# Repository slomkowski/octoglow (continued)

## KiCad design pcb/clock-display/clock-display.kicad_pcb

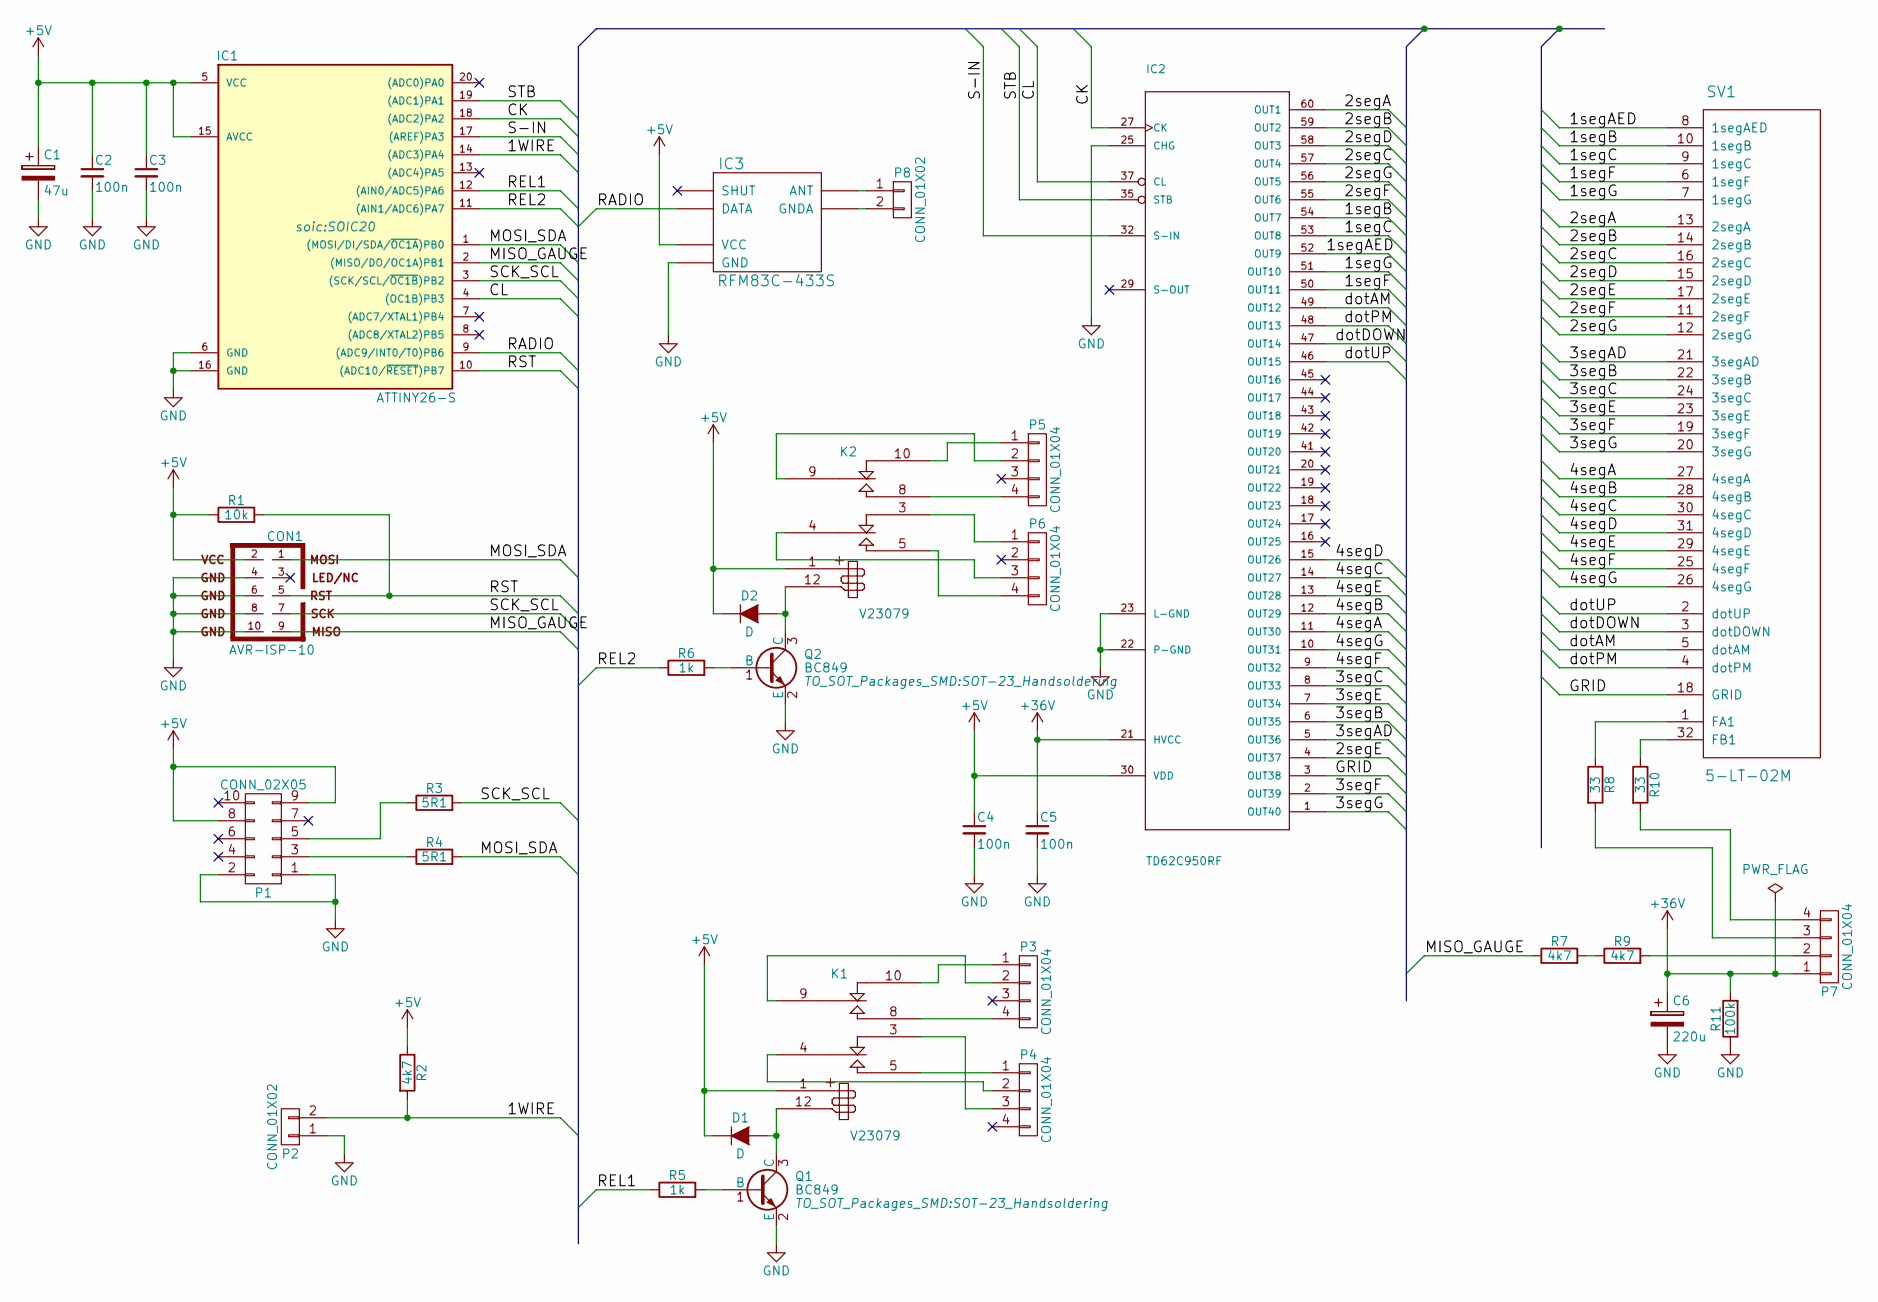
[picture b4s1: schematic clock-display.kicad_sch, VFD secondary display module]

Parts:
C1: 47u; c_elec_8x10
C2, C3, C4, C5: 100n; C_1206_HandSoldering
C6: 220u; c_elec_10x10
CON1: AVR-ISP-10; Pin_Header_Straight_2x05_Pitch2.54mm
D1, D2: D; SMA_Handsoldering
IC1: ATTINY26-S; SOIC20
IC2: TD62C950RF; TD62C950RF-SSOP60-P-0.65A
IC3: RFM83C-433S; RFM83C_standard
K1, K2: V23079; V23098-SMT-long
P1: CONN_02X05; Pin_Header_Straight_2x05_Pitch2.54mm
P2, P8: CONN_01X02; Pin_Header_Straight_1x02_Pitch2.54mm
P3, P4, P7: CONN_01X04; 0-188275-4_SMD_4-pin_female
P5, P6: CONN_01X04; 0-215464-4_TH_4-pin_male
Q1, Q2: BC849; SOT-23_Handsoldering
R1: 10k; R_1206_HandSoldering
R2, R7, R9: 4k7; R_1206_HandSoldering
R3, R4: 5R1; R_1206_HandSoldering
R5, R6: 1k; R_1206_HandSoldering
R8, R10: 33; Resistor_Horizontal_RM15mm
R11: 100k; R_1206_HandSoldering
SV1: 5-LT-02M; futaba-vfd-5-LT-02

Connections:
+5V: C1.1, C2.1, C3.1, C4.1, CON1.2, D1.1 (K), D2.1 (K), IC1.5 (VCC), IC1.15 (AVCC), IC2.30 (VDD), IC2.31 (VDD), IC3.4 (VCC), K1.1 (+), K2.1 (+), P1.8, P1.9, R1.1, R2.1
+36V: C5.1, C6.1, IC2.21 (HVCC), IC2.40 (HVCC), P7.1, R11.2
/1WIRE: IC1.14 ((ADC3)PA4), P2.2, R2.2
/1segAED: IC2.52 (OUT9), SV1.8 (1segAED)
/1segB: IC2.54 (OUT7), SV1.10 (1segB)
/1segC: IC2.53 (OUT8), SV1.9 (1segC)
/1segF: IC2.50 (OUT11), SV1.6 (1segF)
/1segG: IC2.51 (OUT10), SV1.7 (1segG)
/2segA: IC2.60 (OUT1), SV1.13 (2segA)
/2segB: IC2.59 (OUT2), SV1.14 (2segB)
/2segC: IC2.57 (OUT4), SV1.16 (2segC)
/2segD: IC2.58 (OUT3), SV1.15 (2segD)
/2segE: IC2.4 (OUT37), SV1.17 (2segE)
/2segF: IC2.55 (OUT6), SV1.11 (2segF)
/2segG: IC2.56 (OUT5), SV1.12 (2segG)
/3segAD: IC2.5 (OUT36), SV1.21 (3segAD)
/3segB: IC2.6 (OUT35), SV1.22 (3segB)
/3segC: IC2.8 (OUT33), SV1.24 (3segC)
/3segE: IC2.7 (OUT34), SV1.23 (3segE)
/3segF: IC2.2 (OUT39), SV1.19 (3segF)
/3segG: IC2.1 (OUT40), SV1.20 (3segG)
/4segA: IC2.11 (OUT30), SV1.27 (4segA)
/4segB: IC2.12 (OUT29), SV1.28 (4segB)
/4segC: IC2.14 (OUT27), SV1.30 (4segC)
/4segD: IC2.15 (OUT26), SV1.31 (4segD)
/4segE: IC2.13 (OUT28), SV1.29 (4segE)
/4segF: IC2.9 (OUT32), SV1.25 (4segF)
/4segG: IC2.10 (OUT31), SV1.26 (4segG)
/CK: IC1.18 ((ADC2)PA2), IC2.27 (CK)
/CL: IC1.4 ((OC1B)PB3), IC2.37 (CL)
/GRID: IC2.3 (OUT38), SV1.18 (GRID)
/MISO_GAUGE: CON1.9, IC1.2 ((MISO/DO/OC1A)PB1), R7.1
/MOSI_SDA: CON1.1, IC1.1 ((MOSI/DI/SDA/~OC1A)PB0), R4.2
/RADIO: IC1.9 ((ADC9/INT0/T0)PB6), IC3.5 (DATA)
/REL1: IC1.12 ((AIN0/ADC5)PA6), R5.1
/REL2: IC1.11 ((AIN1/ADC6)PA7), R6.1
/RST: CON1.5, IC1.10 ((ADC10/~RESET)PB7), R1.2
/S-IN: IC1.17 ((AREF)PA3), IC2.32 (S-IN)
/SCK_SCL: CON1.7, IC1.3 ((SCK/SCL/~OC1B)PB2), R3.2
/STB: IC1.19 ((ADC1)PA1), IC2.35 (STB)
/dotAM: IC2.49 (OUT12), SV1.5 (dotAM)
/dotDOWN: IC2.47 (OUT14), SV1.3 (dotDOWN)
/dotPM: IC2.48 (OUT13), SV1.4 (dotPM)
/dotUP: IC2.46 (OUT15), SV1.2 (dotUP)
GND: C1.2, C2.2, C3.2, C4.2, C5.2, C6.2, CON1.4, CON1.6, CON1.8, CON1.10, IC1.6 (GND), IC1.16 (GND), IC2.22 (P-GND), IC2.23 (L-GND), IC2.25 (CHG), IC2.38 (L-GND), IC2.39 (P-GND), IC3.6 (GND), P1.1, P1.2, P2.1, Q1.2 (E), Q2.2 (E), R11.1
unnamed: D1.2 (A), K1.12 (-), Q1.3 (C)
unnamed: D2.2 (A), K2.12 (-), Q2.3 (C)
unnamed: IC3.1 (ANT), P8.1
unnamed: IC3.2 (GNDA), P8.2
unnamed: K1.4 (C1), P4.2
unnamed: K1.9 (C2), P3.2
unnamed: K1.3 (R1), P4.3
unnamed: K1.10 (R2), P3.1
unnamed: K1.5 (T1), P4.1
unnamed: K1.8 (T2), P3.4
unnamed: K2.4 (C1), P6.3
unnamed: K2.9 (C2), P5.2
unnamed: K2.3 (R1), P6.1
unnamed: K2.10 (R2), P5.1
unnamed: K2.5 (T1), P6.4
unnamed: K2.8 (T2), P5.4
unnamed: P1.3, R4.1
unnamed: P1.5, R3.1
unnamed: P7.2, R9.2
unnamed: P7.3, R8.2
unnamed: P7.4, R10.2
unnamed: Q1.1 (B), R5.2
unnamed: Q2.1 (B), R6.2
unnamed: R7.2, R9.1
unnamed: R8.1, SV1.1 (FA1)
unnamed: R10.1, SV1.32 (FB1)

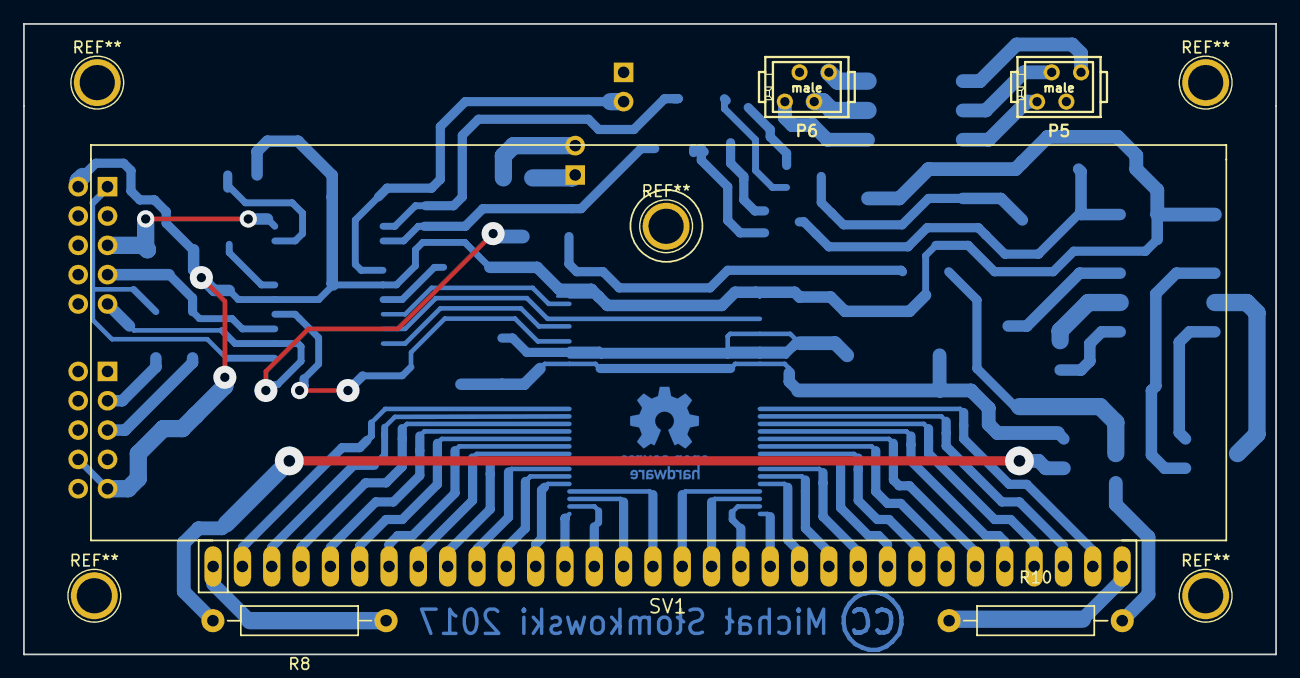
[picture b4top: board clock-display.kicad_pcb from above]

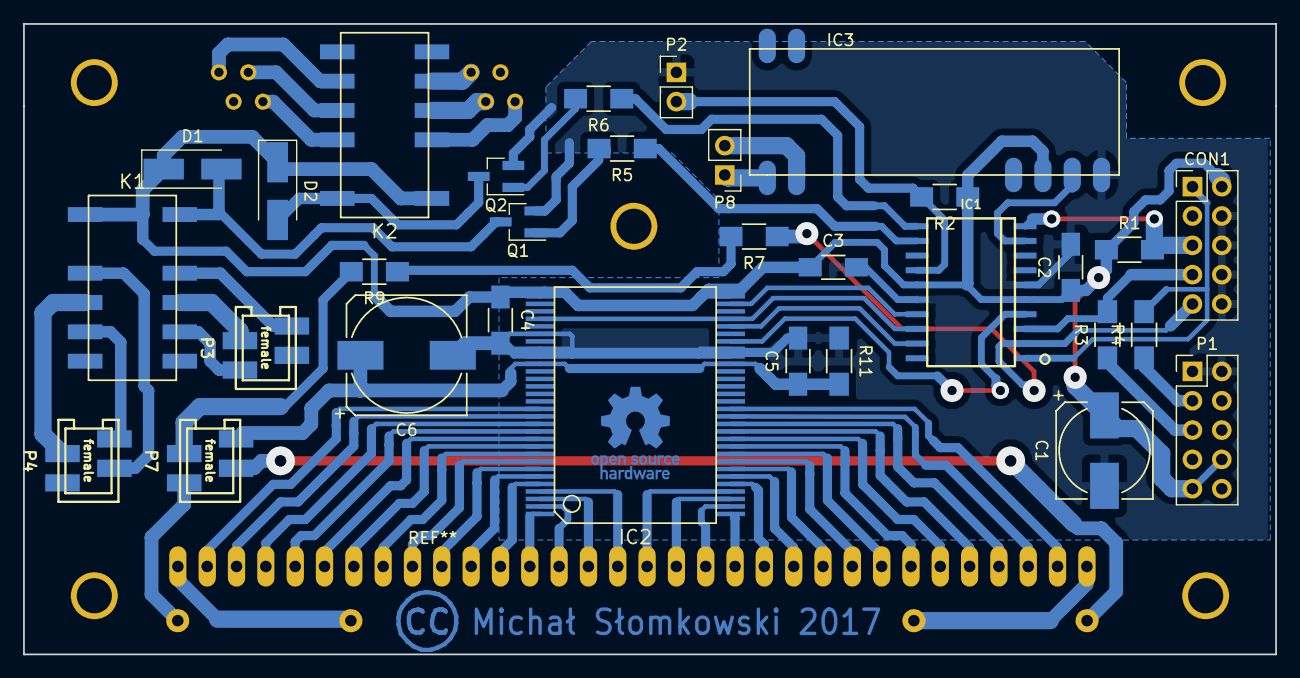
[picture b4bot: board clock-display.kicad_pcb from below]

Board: 2 copper layers, 108.5 x 54.6 mm, 36 parts (31 on the bottom side), 71 nets.

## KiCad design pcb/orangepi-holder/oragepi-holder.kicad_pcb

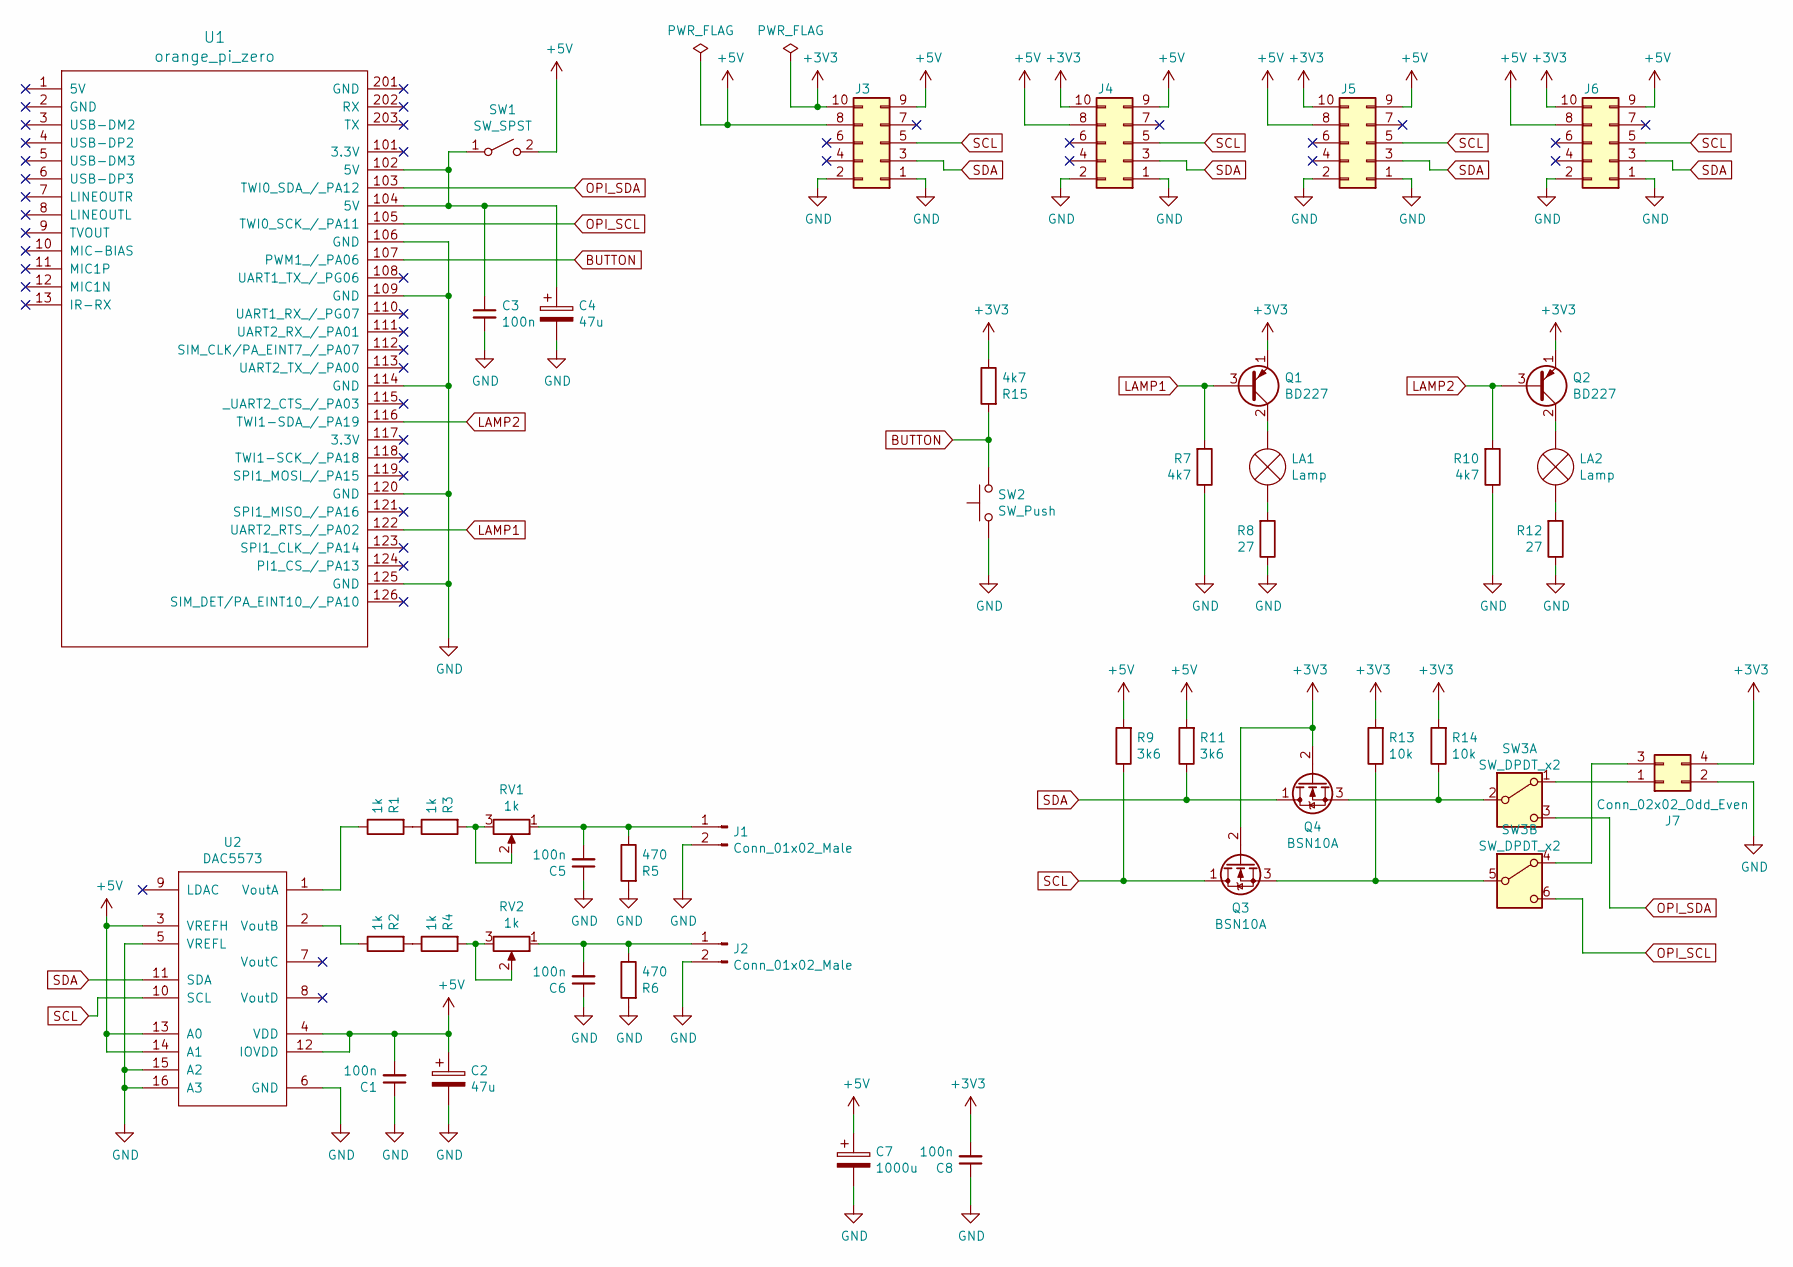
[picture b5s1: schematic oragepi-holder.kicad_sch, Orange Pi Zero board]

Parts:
C1, C3, C5, C6, C8: 100n; C_1206_HandSoldering
C2, C4: 47u; CP_Radial_D7.5mm_P2.50mm
C7: 1000u; CP_Axial_L30.0mm_D10.0mm_P35.00mm_Horizontal
J1, J2: Conn_01x02_Male; Pin_Header_Angled_1x02_Pitch2.54mm
J3, J4, J5, J6: Conn_02x05_Odd_Even; IDC-Header_2x05_P2.54mm_Vertical
J7: Conn_02x02_Odd_Even; 0-215464-4_TH_4-pin_male
LA1, LA2: Lamp; Pin_Header_Straight_1x02_Pitch2.00mm
Q1, Q2: BD227; TO-126_Vertical
Q3, Q4: BSN10A; TO-92_Molded_Wide_Oval
R1, R2, R3, R4: 1k; R_1206_HandSoldering
R5, R6: 470; R_1206_HandSoldering
R7, R10: 4k7; R_1206_HandSoldering
R8, R12: 27; R_Axial_DIN0414_L11.9mm_D4.5mm_P15.24mm_Horizontal
R9, R11: 3k6; R_Axial_DIN0411_L9.9mm_D3.6mm_P15.24mm_Horizontal
R13, R14: 10k; R_Axial_DIN0411_L9.9mm_D3.6mm_P15.24mm_Horizontal
R15: 4k7; R_Axial_DIN0411_L9.9mm_D3.6mm_P15.24mm_Horizontal
RV1, RV2: 1k; SP5-2
SW1: SW_SPST; SPDT
SW2: SW_Push; SPDT
SW3: SW_DPDT_x2; APEM_5246
U1: orange_pi_zero; orangepi-zero
U2: DAC5573; TSSOP-16_4.4x5mm_Pitch0.65mm

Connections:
+3V3: C8.2, J3.10, J4.10, J5.10, J6.10, J7.4, Q1.1 (E), Q2.1 (E), Q3.2 (G), Q4.2 (G), R13.2, R14.2, R15.1
+5V: C1.2, C2.1, C7.1, J3.8, J3.9, J4.8, J4.9, J5.8, J5.9, J6.8, J6.9, R9.2, R11.2, SW1.2 (B), U2.3 (VREFH), U2.4 (VDD), U2.12 (IOVDD), U2.13 (A0), U2.14 (A1)
BUTTON: R15.2, SW2.2, U1.107 (PWM1_/_PA06)
GND: C1.1, C2.2, C3.2, C4.2, C5.1, C6.1, C7.2, C8.1, J1.2, J2.2, J3.1, J3.2, J4.1, J4.2, J5.1, J5.2, J6.1, J6.2, J7.2, R5.2, R6.2, R7.1, R8.1, R10.1, R12.1, SW2.1, U1.106 (GND), U1.109 (GND), U1.114 (GND), U1.120 (GND), U1.125 (GND), U2.5 (VREFL), U2.6 (GND), U2.15 (A2), U2.16 (A3)
LAMP1: Q1.3 (B), R7.2, U1.122 (UART2_RTS_/_PA02)
LAMP2: Q2.3 (B), R10.2, U1.116 (TWI1-SDA_/_PA19)
unnamed: C5.2, J1.1, R5.1, RV1.1
unnamed: C6.2, J2.1, R6.1, RV2.1
unnamed: J7.1, SW3.1 (A)
unnamed: J7.3, SW3.4 (A)
unnamed: LA1.2 (+), Q1.2 (C)
unnamed: LA1.1 (-), R8.2
unnamed: LA2.2 (+), Q2.2 (C)
unnamed: LA2.1 (-), R12.2
unnamed: Q3.3 (S), R13.1, SW3.5 (B)
unnamed: Q4.3 (S), R14.1, SW3.2 (B)
unnamed: R1.2, R3.1
unnamed: R2.2, R4.1
unnamed: R3.2, RV1.2, RV1.3
unnamed: R4.2, RV2.2, RV2.3
unnamed: C3.1, C4.1, SW1.1 (A), U1.102 (5V), U1.104 (5V)
unnamed: R1.1, U2.1 (VoutA)
unnamed: R2.1, U2.2 (VoutB)
OPI_SCL: SW3.6 (C), U1.105 (TWI0_SCK_/_PA11)
OPI_SDA: SW3.3 (C), U1.103 (TWI0_SDA_/_PA12)
SCL: J3.5, J4.5, J5.5, J6.5, Q3.1 (D), R9.1, U2.10 (SCL)
SDA: J3.3, J4.3, J5.3, J6.3, Q4.1 (D), R11.1, U2.11 (SDA)

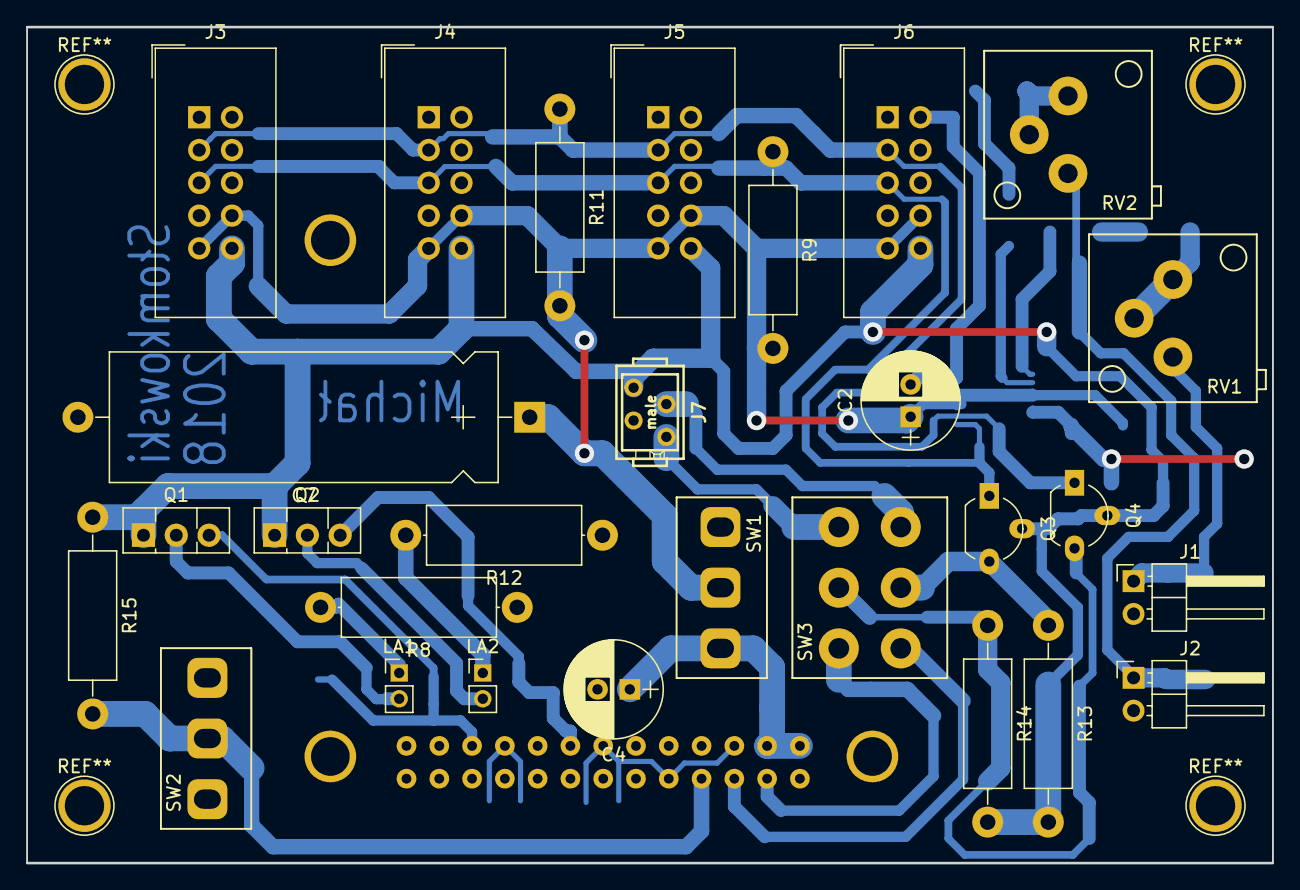
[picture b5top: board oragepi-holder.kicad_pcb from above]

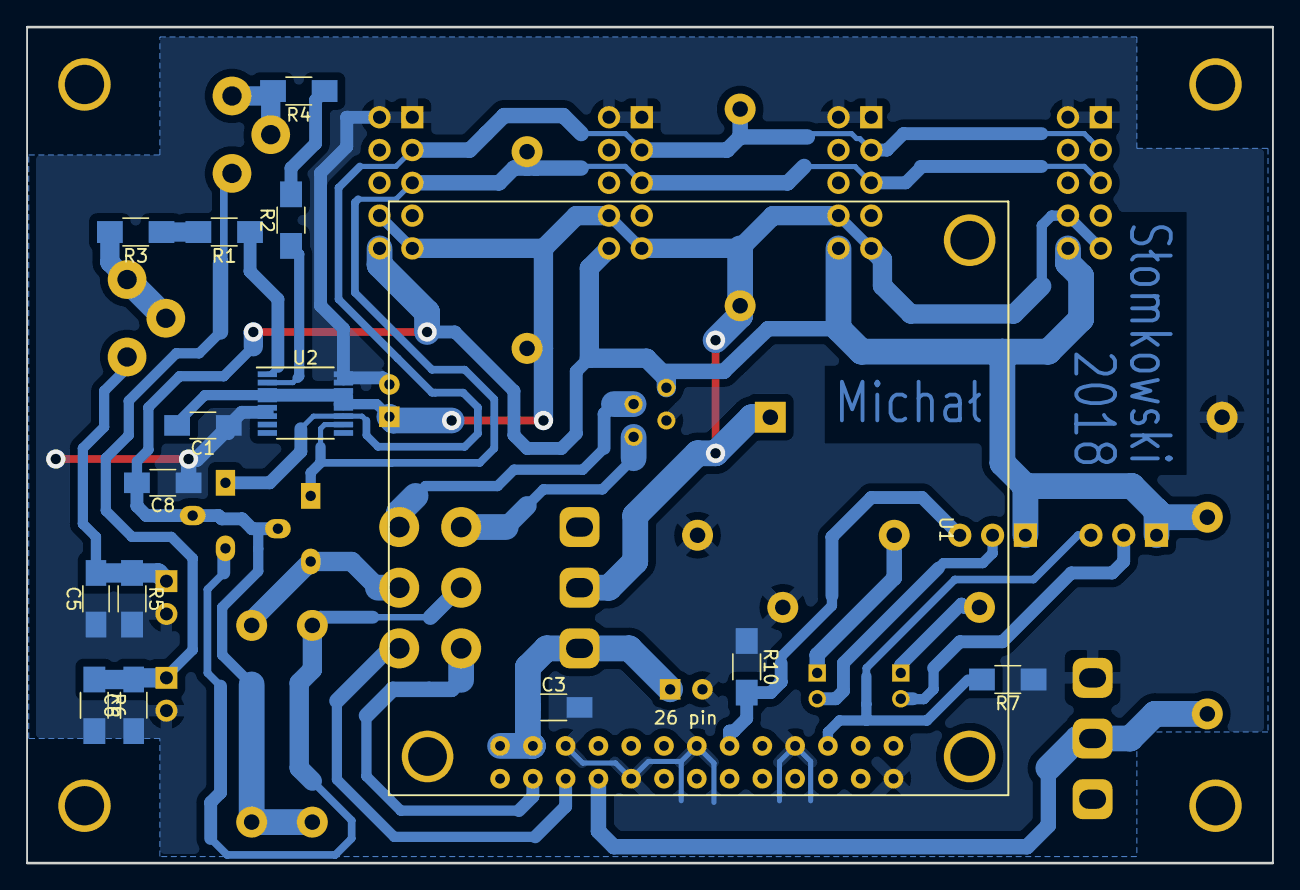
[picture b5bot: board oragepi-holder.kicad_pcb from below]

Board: 2 copper layers, 96.5 x 64.8 mm, 43 parts (15 on the bottom side), 27 nets.

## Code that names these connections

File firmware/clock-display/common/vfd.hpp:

/*
 * VFD driver hardware shared by the application (src/) and the bootloader (bootloader/).
 * The VFD is statically driven by a 40-bit shift register: CK - clock, S_IN - data, STB - latch.
 * CL is the blanking input, PWM on OC1B sets the brightness.
 */
#pragma once

#include <inttypes.h>
#include <avr/io.h>
#include <avr/pgmspace.h>

namespace octoglow::vfd_clock::vfd {
    constexpr uint8_t CK_PIN = PA2;
    constexpr uint8_t STB_PIN = PA1;
    constexpr uint8_t S_IN_PIN = PA3;
    constexpr uint8_t CL_PIN = PB3;

    constexpr uint8_t NUMBER_OF_POSITIONS = 4;
    constexpr uint8_t NUMBER_OF_SEGMENTS = 40;
    constexpr uint8_t SEGMENT_BUFFER_SIZE = NUMBER_OF_SEGMENTS / 8;

    constexpr uint8_t ALWAYS_ON_SEGMENT = 37; // 0-based bit in the segment buffer
    constexpr uint8_t UPPER_DOT_SEGMENT = 14;
    constexpr uint8_t LOWER_DOT_SEGMENT = 13;

    // the dots are in the second byte of the segment buffer
    constexpr uint8_t UPPER_DOT = 1 << (UPPER_DOT_SEGMENT % 8);
    constexpr uint8_t LOWER_DOT = 1 << (LOWER_DOT_SEGMENT % 8);
    static_assert(UPPER_DOT_SEGMENT / 8 == 1 and LOWER_DOT_SEGMENT / 8 == 1);

    static constexpr uint8_t BRIGHTNESS_PWM_VALUES[] PROGMEM = {0, 1, 4, 10, 20, 60};
    constexpr uint8_t DEFAULT_BRIGHTNESS = 3;

    /*
     * rows - display number
     * cols - segments a-g, 1-based segment number
     */
    static constexpr uint8_t SEGMENT_ORDERING[] PROGMEM = {
        9, 7, 8, 9, 9, 11, 10,
        1, 2, 4, 3, 37, 6, 5,
        36, 35, 33, 36, 34, 39, 40,
        30, 29, 27, 26, 28, 32, 31
    };

    static_assert(sizeof(SEGMENT_ORDERING) == NUMBER_OF_POSITIONS * 7, "ordering doesn't sum to 4 chars x 7 segments");

    /*
     *      aaaaaa
     *     f      b
     *     f      b
     *     f      b
     *      gggggg
     *     e      c
     *     e      c
     *     e      c
     *      dddddd
     *
     * bit 0 - a, ..., bit 6 - g
     */
    static constexpr uint8_t CHARACTER_SHAPES[] PROGMEM = {
        0b0000000,
        0b0111111,
        0b0000110,
        0b1011011,
        0b1001111,
        0b1100110,
        0b1101101,
        0b1111101,
        0b0000111,
        0b1111111,
        0b1100111,
        0b1000000,
        0b0001000,
        0b0110001,
    };

    static constexpr char CHARACTER_ORDER[] PROGMEM = {
        ' ', '0', '1', '2', '3', '4', '5', '6', '7', '8', '9', '-', '_', 'T'
    };

    static_assert(sizeof(CHARACTER_SHAPES) == sizeof(CHARACTER_ORDER),
                  "every char shape has to have character defined");

    struct SegmentBuffer {
        uint8_t bytes[SEGMENT_BUFFER_SIZE];
    };

    /**
     * Compile-time only (reads PROGMEM tables directly): the segment buffer for the given character shapes.
     */
    consteval SegmentBuffer segmentsForShapes(const uint8_t (&shapes)[NUMBER_OF_POSITIONS]) {
        SegmentBuffer buffer{};
        buffer.bytes[ALWAYS_ON_SEGMENT / 8] |= 1 << (ALWAYS_ON_SEGMENT % 8);

        for (uint8_t position = 0; position != NUMBER_OF_POSITIONS; ++position) {
            for (uint8_t s = 0; s != 7; ++s) {
                if (shapes[position] & 1 << s) {
                    const uint8_t segment = SEGMENT_ORDERING[7 * position + s] - 1;
                    buffer.bytes[segment / 8] |= 1 << (segment % 8);
                }
            }
        }

        return buffer;
    }

    consteval uint8_t shapeOf(const char character) {
        for (uint8_t c = 0; c != sizeof(CHARACTER_ORDER); ++c) {
            if (CHARACTER_ORDER[c] == character) {
                return CHARACTER_SHAPES[c];
            }
        }
        __builtin_unreachable(); // compile error: character not supported
    }

    inline void initPins() {
        DDRA |= _BV(CK_PIN);
        DDRA |= _BV(STB_PIN);
        DDRA |= _BV(S_IN_PIN);
    }

    inline void setBrightnessPwm(const uint8_t pwmValue) {
        OCR1B = pwmValue;
    }

    /**
     * Timer1 runs at clk / 128, PWM on OC1B (CL pin). The application also uses its overflow as a time base.
     */
    inline void initBrightnessPwm(const uint8_t pwmValue) {
        DDRB |= _BV(CL_PIN);
        TCCR1A = _BV(COM1B1) | _BV(PWM1B);
        TCCR1B = _BV(PSR1) | _BV(CS13);
        setBrightnessPwm(pwmValue);
    }

    /**
     * Shifts the segment buffer out, the last segment first, and latches it.
     */
    inline void loadSegments(const uint8_t (&segments)[SEGMENT_BUFFER_SIZE]) {
        PORTA &= ~_BV(STB_PIN);

        for (uint8_t idx = SEGMENT_BUFFER_SIZE; idx != 0; --idx) {
            const uint8_t byte = segments[idx - 1];

            for (uint8_t mask = 0x80; mask != 0; mask >>= 1) {
                PORTA &= ~_BV(CK_PIN);

                if (byte & mask) {
                    PORTA |= _BV(S_IN_PIN);
                } else {
                    PORTA &= ~_BV(S_IN_PIN);
                }

                PORTA |= _BV(CK_PIN);
            }
        }

        PORTA |= _BV(STB_PIN);
    }
}

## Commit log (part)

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2016-05-27 Add Eagle library with VFD display.
2016-07-20 Add work in progress board and libraries.
2016-07-20 Update.
2016-10-20 Board beta complete.
2016-10-22 Make some lines thicker.
2016-10-28 Update resistor values.
2016-11-27 Move files to valid PCB dir.
2016-11-29 Add template for AVR firmware.
2016-12-03 Add displaying characters in 5x7 format.
2016-12-03 Add demo text display.
2016-12-07 Add font converted to original LCD format.
2016-12-12 Add 2-LT-05 component.
2016-12-12 Add footprint for 5-LT-02.
2016-12-12 Move display-front to subdir.
2017-01-09 Add clock schematic and some elements.
2017-01-12 Add receiver library element. Finish clock board.
2017-01-15 Add stub for clock board firmware.
    Implement displaying numbers on display.
2017-01-16 Add speaker stub, change VFD display code to use frame buffer.
2017-01-24 Add working impl of cell mode scrolling text.
2017-01-25 Add working impl of column mode scroll.
2017-01-25 Add static text mode.
2017-01-27 Add complete display demo.
2017-01-27 Add invalid character support.
2017-01-29 Add relay support. Add brightness setting and dot support.
2017-02-05 Add I2C support.
2017-02-09 Implement weather sensor support. Add I2C request parser.
2017-02-14 Do some optimizations.
2017-07-30 Add case sketch.
2017-09-10 Add hello world for MSP430.
2017-10-09 Add some libraries for Geiger.
2017-10-15 Add Geiger, transformer models.
2017-10-25 Add almost complete Geiger schematic (without connections to MCU).
2017-10-25 Update schematic numbering.
2017-11-10 Further pcb changes.
2017-11-13 Finish Geiger schematic.
2017-11-17 Finish Geiger board.
2017-11-27 Update element values on the schematic.
2017-11-29 Add support for ADC in geiger.
2018-01-18 Add support for eye inverter, add fixed ADC and timer subsystem.
2018-01-18 Add eye inverter states.
2018-01-19 Separate some code in Geiger to common module. Add unit test harness. Create unit test for eye.
2018-02-22 Further changes in Geiger firmware.
2018-02-25 Add code skeleton for counting.
2018-02-26 Add animation testing application.
2018-02-28 Fix I2C slave working.
2018-03-04 Add some animation draft.
2018-03-04 Add PDF of case side.
2018-03-04 Update gitignore.
2018-03-04 Refactor Geiger project to match new structure.
2018-03-05 Add beta animation procedure based on libfixmath.
2018-03-05 Refactor animation code to use fix16_t instead of Fix16.
2018-03-14 Add script to read weather data using I2C.
2018-03-29 Add new libraries for new Geiger board.
2018-04-10 All connections ready.
2018-04-11 Add every feature on the board. Beta.
2018-04-11 Final version of geiger board.
2018-04-17 Change some element values geiger.
2018-04-20 Update geiger element values.
2018-04-21 Tweak geiger code animation and inverters.
2018-04-21 Update element values on geiger board.
2018-04-21 Change to display read temperature.
2018-04-24 Add support for brightness of the eye.
2018-04-25 Add Rust application template.
2018-05-03 Add project initialization of Kotlin octoglowd.
2018-05-03 Add script to enable eye.
2018-05-05 Add Actix skeleton. Implement updating clock display.
2018-05-05 Implement I2C command executor.
2018-05-06 Implement tests for I2C for front.
2018-05-07 Add further implementation of I2C commands. NOT COMPILING
2018-05-08 Change to use registry as actor holder. Implement scrolling text message.
2018-05-12 Implement set graphics command.
2018-05-14 Fix problem with compilation when using `then`.
2018-05-15 Implement unit test for I2C. Add logger. Refactor.
2018-05-20 Add config file support.
2018-05-21 Add draft of view of temperature.
2018-05-23 Add support for drawing charts from sequences.
2018-05-25 Add inside weather view implementation.
2018-05-26 Implement async I2C without read.
2018-05-27 Add database support.
2018-06-04 Manage to circumvent the lifetime problem using Cell and RefCell.
2018-06-12 Add common trait for views.
2018-06-20 Implement outside weather view.
2018-06-20 Add clock support.
2018-06-25 Add geiger view draft. Add some geiger I2C commands.
2018-07-19 Enable something.
2018-07-19 Add abstraction layer for I2C bus.
2018-10-20 Add CP2112 speed set.
2018-10-28 Add OrangePi holder PCB project.
2018-10-31 Add some lib symbols, add all components to schematic.
2018-11-17 Finished schematic and pcb for orange pi.
2018-11-18 Final orange pi board.
2018-11-29 Update all Kicad files to Kicad 5.
2019-01-11 Add skeleton implementation of Kotlin code.
2019-01-11 Add more complete API impl.
2019-01-21 Implement SQL query generator for avg series.
2019-01-24 Implement base front display controller, fix various things.
2019-01-26 Changes to run hardware in dedicated thread.
2019-01-26 Implement config file manager.
2019-01-26 Move to other package.
2019-01-26 Change OutdoorTemp format, add sanity check in clock.
2019-01-27 Change OutdoorReport to new format.
2019-01-28 Add some code.
2019-01-28 Implement ranges and baseline test for brightness.
2019-01-29 Add base impl of cryptocurrency view.
2019-01-30 Implement brightness support.
2019-01-31 Refactor controllers to Controller class.
2019-02-01 Refactor controller to daemons.
2019-02-01 Move views to controller package
2019-02-02 Add cryptocurrency historical data view.
2019-02-15 Add BME280 initialization code.
2019-02-24 Limit Geiger PWM to 28%.
2019-03-03 Add ticking fix - use 8MHz normally, switch to 16 MHz for I2C transmission.
2019-03-03 Add retry pattern to I2C read from Geiger.
2019-03-03 Update values on PCB.
2019-03-11 Add some code for Geiger view.
2019-03-11 Add flag about completion to Geiger. Implement Geiger view.
2019-03-12 Fix assembly plugin, add some exclusions.
2019-03-12 Configure shade plugin.
2019-03-13 Add google concurrent to ignore list.
2019-03-17 Add stub for Calendar view.
2019-03-18 Implement Calendar view.
2019-03-19 Add separate brightness tests. Fix CalendarView.
2019-03-20 Add menu objects.
2019-03-21 Add some menu impl.
2019-03-27 Update new brightness PWM values for clock display.
2019-03-27 Add stub test for states.
2019-03-28 Add bell support.
2019-03-28 Add some menu support.
2019-03-28 Implement full menu navigation.
2019-03-30 Changes to use common pool for coroutines. Implement brightness setting in DB.
2019-03-30 Fix tests.
2019-03-31 Remove some todos, limit cryptocurrencies list to 200.
2019-04-02 Fix bug with reading negative value from encoder.
2019-04-02 Add stub of NetworkView.
2019-04-03 Add some code for ping support.
2019-04-03 Add impl of parsing /proc/net/route, fix ping parse.
2019-04-08 Add preferred display time.
2019-04-08 Implement cycling over views.
2019-04-09 Bump C++ to 17. Fix firmware tests.
2019-04-16 Implement BME280 support.
2019-04-16 Implement BME280 view. Add MSL pressure support.
2019-04-22 Remove old octoglowd in Rust.
2019-04-23 Implement NBP exchange rates download.
2019-04-23 Implement base error handler.
2019-04-23 Implement exception handler for everything except hardware.
2019-04-24 Minor fixes, update dependencies, change POM to have smaller JAR.
2019-04-25 Fix reading data from BME280. Remove humidity from DB and views. Integrate indoor and outdoor into one view.
2019-05-05 Update README.
2019-05-05 Fix indoor weather drawing.
2019-05-09 Bump konf version. Implement validators for geo.
2019-05-16 Add photo.
2019-06-13 Make cycling time shorter.
2019-06-30 Add implement downloading of content from Simplemonitor instance.
2019-06-30 Add additional messages to text length assertions.
2019-08-17 Fix SimpleMonitor bug.
2019-08-19 Add offset to indoor temp sensor due to self heating.
2020-05-09 Add changeable setting of ring on fail for SimpleMonitor.
2020-05-10 Fix network view.
2020-05-10 Fix Coinpaprika API access.
2020-05-26 Fix various issues in octoglowd.
2020-08-14 Update SimpleMonitor view to support datetime with offset.
2020-10-03 Implement stock download from Stooq. #3
2020-10-09 Fix stock download. #3
2020-11-19 Change single thread to Mutex in I2C.
2020-12-02 Fix various messages, implement stock info saving.
2020-12-06 Change all LocalDateTime to ZonedDateTime.
2021-01-29 Move Wi-Fi info to AnalogGaugeDaemon.
2021-01-30 Add gateway ping.
2021-01-30 Update all dependencies.
2021-02-01 Fix negative temperature read.
2021-02-13 Replace Fuel with Ktor.
2021-02-15 Implement air quality.
2021-03-14 Change weather sensor to SP67. #5
2021-04-09 Implement Fanju sensor support. #5
2021-04-12 Implement Fanju sensor weather view. Replace most of Java Time with kotlinx.time. #5
2021-06-21 Remove BME280 support, add humidity to weather report.
2021-06-21 Update dependencies.
2021-07-28 Add I2C error handler.
2023-03-05 Increase coinpaprika query interval. Update air quality tests.
2023-06-19 Fix air quality test.
2023-06-19 Fix buffer overflow for scrolling text.
2023-06-19 Bump dependencies.
2023-06-21 Change encoder code.
2023-06-21 Change pool interval for front display.
2023-06-22 Remove java.time from everywhere except config.
2023-06-25 Remove mutex from hardware, run in separate thread.
2023-06-25 Testing snakeyaml-kmp.
2023-11-29 Bump ch.qos.logback:logback-classic in /software/octoglowd
    Bumps [ch.qos.logback:logback-classic](https://github.com/qos-ch/logback) from 1.4.8 to 1.4.12.
    - [Commits](https://github.com/qos-ch/logback/compare/v_1.4.8...v_1.4.12)
    ---
    updated-dependencies:
    - dependency-name: ch.qos.logback:logback-classic
    dependency-type: direct:production
2025-05-22 Remove uchuhimo konf library. Bundle stateful4k libr.
2025-05-28 Add autogenerated Gradle project.
2025-05-29 Clean up Gradle.
2025-05-29 Replace exposed with SQLDelight.
2025-06-02 Replace Logback with Tinylog.
2025-06-08 Rewrite coroutine architecture.
2025-06-10 Move preferredDisplayTime to property. FrontDisplayDaemon tweaks.
2025-06-18 Fix bugs with scrolling text overflow.
2025-06-19 Add averaging for analog gauges.
2025-06-19 Add some code for SCD40, refactor I2C code.
2025-06-24 Implement CRC8 for I2C - clock display.
2025-06-24 Clang tidy front-display.
2025-06-24 A lot of changes, add BME280 and SCD40 support prelineary.
2025-06-25 Add mock implementation of FrontDisplay.
2025-06-26 Implement setting construction date to intro message in front display.
2025-06-26 Slight optimization.
2025-07-01 Implement SCD40 view and hardware.
2025-07-01 Rewrite I2C code to use IntArray instead of I2CBuffer. Various optimizations.
2025-07-01 Change the clock display protocol to have CRC8 at the first byte.
2025-07-03 Various changes for Geiger, add I2C CRC8.
2025-07-04 Add PID controller to inverter eye.
2025-07-05 Various tests for Geiger in octoglowd.
2025-07-05 Refactor I2C classes, cleanup.
2025-07-06 Tweak Geiger code, fix tests.
2025-07-14 Add reporting of light sensor value to MQTT.
2025-07-14 Adjust clock brightness PWM levels.
2025-07-15 Add schematic for rotary encoder board.
2025-07-21 Rotary encoder board.
2025-07-23 Remove commons-lang3. Add light sensor support in brightness demon. Move Homeassistant package.
2025-07-29 Add enhanced encoder implementation.
2025-08-01 Implement data collectors.
2025-08-01 Refactor.
2025-08-01 Implement dial control via Homeassistant.
2025-08-03 Clean up MQTT sending. Implement setting the magic eye from MQTT.
2025-08-07 Implement connection monitoring for MQTT. Change NetworkView.
2025-08-08 Change Todoist view.
2025-08-12 Remove old views.
2025-08-12 Bump kotlinx-datetime to 0.7.2.
2025-08-13 Add garbage collection timetable support.
2025-08-25 Bump ktor-mqtt to 0.7.0.
2025-08-26 Fix publication of eye state to MQTT on reconnecting.
2025-09-19 Tweak Geiger code.
2025-10-03 Migrate to KiCAD 9.
2025-10-03 Removed old KiCAD files.
2025-10-05 Add polling of eye state to monitor changes if ie. board restart.
2025-10-23 Add counter to trigger reconnection with MQTT.
2025-10-29 Update website URL-s.
2025-11-25 Bump libs.
2025-12-01 Fix trash pickup view.
2026-02-02 Implement support for getting relay state.
2026-02-02 Add drawing of backlight case.
2026-02-13 Implement shopping Sunday algorithm.
